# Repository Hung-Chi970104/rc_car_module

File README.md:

# Rukus: Pocket Robotics Control Computer
Welcome to Rukus! The most powerful and versatile pocket-size robotic control computer that can handle up 18V and 3.2A of peak current. It also features a powerful dual-core RP2040 MCU, allowing users to run heavy computing and even TinyML!

## Demo Video
https://github.com/user-attachments/assets/a237940f-da78-4733-91b2-979578ba8ca9

https://github.com/user-attachments/assets/f6da3c5c-2f20-4054-9eab-c4b8ad8e2e0a

## Components
- RP2040
- 12MHz Crystal (ABM8-272-T3)
- 4MB Flash Storage (W25Q16JVUXIQ)
- Buck-Boost Switching Regulator 5V to 3V3 (RT6150BGQW)
- Buck-Boost Switching Regulator 12V to 5V (AP64201)
- USB-C (TYPE-C-31-M-12)
- Motor Driver (TB6612FNG)

## PCBs
- 2 layers
- Single-sided component placement
- 2.6mm board thickness
- HASL (with lead) surface finish
- 1oz outer copper weight

### PCB Schematic

### PCB Layouts

### 3D Model

# How to order
- Download the zip file
- Upload the zip file to JLCPCB
- Select PCBA and continue
- Upload BOM.csv and position.csv
- Select the parts and submit payment

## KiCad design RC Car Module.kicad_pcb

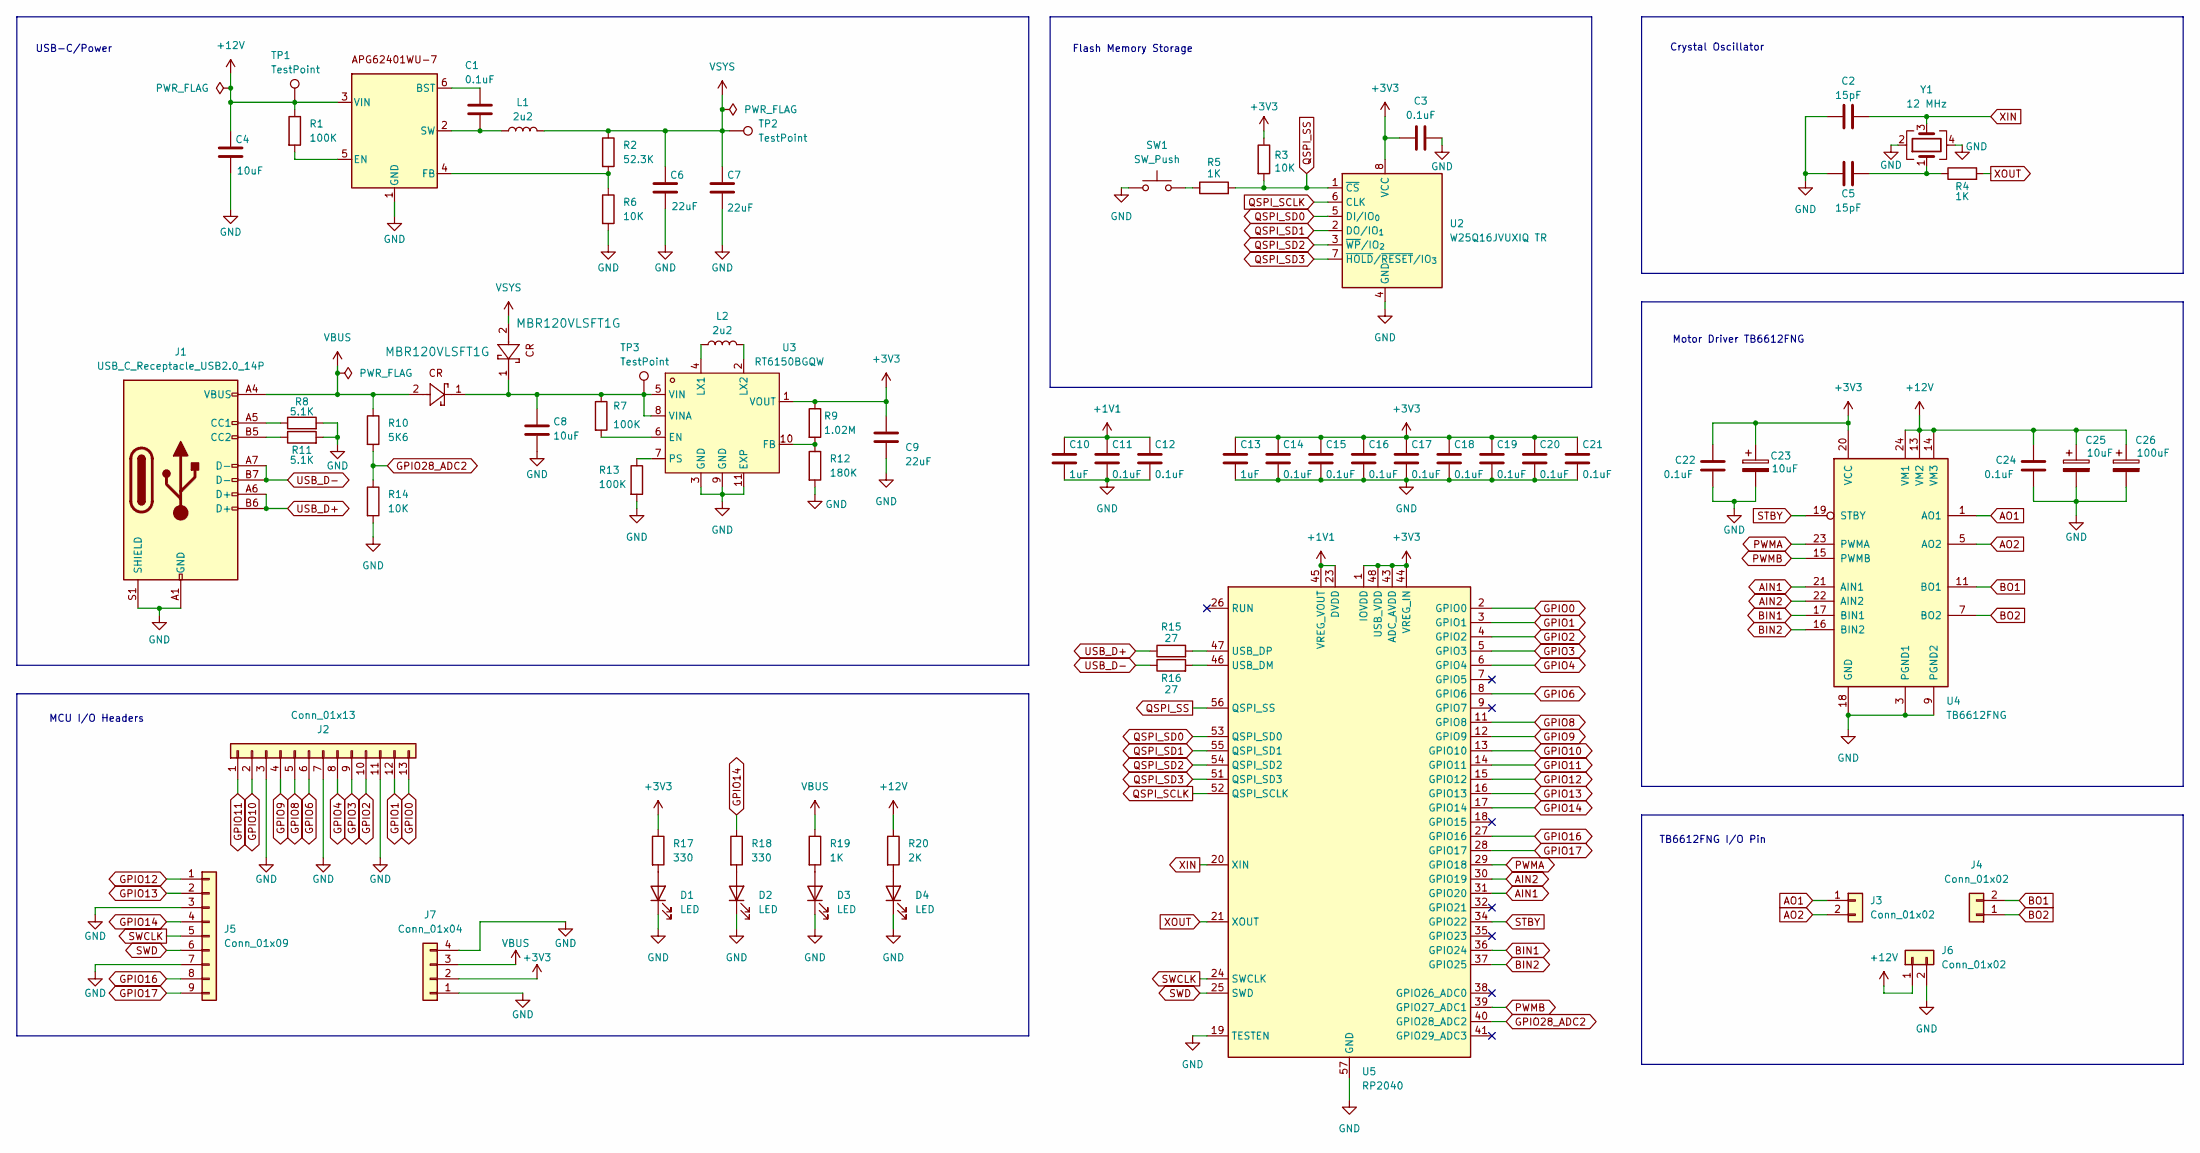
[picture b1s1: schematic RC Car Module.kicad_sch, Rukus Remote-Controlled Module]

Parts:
1111111111111, 11111111111111: MBR120VLSFT1G; SDO_SOD-123FL_ONS
C1, C3, C11, C12, C14, C15, C16, C17, C18, C19, C20, C21, C22, C24: 0.1uF; C_0402_1005Metric
C2, C5: 15pF; C_0402_1005Metric
C4, C8: 10uF; C_1206_3216Metric
C6, C7, C9: 22uF; C_1206_3216Metric
C10, C13: 1uF; C_0402_1005Metric
C23, C25: 10uF; CP_EIA-3528-15_AVX-H
C26: 100uF; CP_Elec_6.3x7.7
D1, D2, D3, D4: LED; LED_0805_2012Metric
J1: USB_C_Receptacle_USB2.0_14P; USB_C_Receptacle_HRO_TYPE-C-31-M-12
J2: Conn_01x13; PinHeader_1x13_P2.54mm_Vertical
J3, J4, J6: Conn_01x02; TerminalBlock_Phoenix_MKDS-1,5-2-5.08_1x02_P5.08mm_Horizont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
J5: Conn_01x09; PinHeader_1x09_P2.54mm_Vertical
J7: Conn_01x04; PinHeader_1x04_P2.54mm_Vertical
L1: 2u2; IND-SMD_L4.0-W4.0_XAL4030-332MEC
L2: 2u2; L_1008_2520Metric
R1, R7, R13: 100K; R_0402_1005Metric
R2: 52.3K; R_0402_1005Metric
R3, R6, R14: 10K; R_0402_1005Metric
R4, R5, R19: 1K; R_0402_1005Metric
R8, R11: 5.1K; R_0402_1005Metric
R9: 1.02M; R_0402_1005Metric
R10: 5K6; R_0402_1005Metric
R12: 180K; R_0402_1005Metric
R15, R16: 27; R_0402_1005Metric
R17, R18: 330; R_0402_1005Metric
R20: 2K; R_0402_1005Metric
SW1: SW_Push; SW_Push_SPST_NO_Alps_SKRK
TP1, TP2, TP3: TestPoint; TestPoint_Pad_1.0x1.0mm
U1: AP62401WU-7; SOT-23-6
U2: W25Q16JVUXIQ TR; Winbond_USON-8-1EP_3x2mm_P0.5mm_EP0.2x1.6mm
U3: RT6150BGQW; WSON-10_L2.5-W2.5-P0.50-BL-EP; LCSC Part C147972
U4: TB6612FNG; SSOP-24_5.3x8.2mm_P0.65mm
U5: RP2040; QFN-56-1EP_7x7mm_P0.4mm_EP3.2x3.2mm
Y1: 12 MHz; Crystal_SMD_3225-4Pin_3.2x2.5mm

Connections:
+1V1: C10.1, C11.1, C12.1, U5.23 (DVDD), U5.45 (VREG_VOUT), U5.50 (DVDD)
+3V3: C3.1, C9.1, C13.1, C14.1, C15.1, C16.1, C17.1, C18.1, C19.1, C20.1, C21.1, C22.1, C23.1, J7.2, R3.1, R9.1, R17.1, U2.8 (VCC), U3.1 (VOUT), U4.20 (VCC), U5.1 (IOVDD), U5.10 (IOVDD), U5.22 (IOVDD), U5.33 (IOVDD), U5.42 (IOVDD), U5.43 (ADC_AVDD), U5.44 (VREG_IN), U5.48 (USB_VDD), U5.49 (IOVDD)
+12V: C4.1, C24.1, C25.1, C26.1, J6.1, R1.1, R20.1, TP1.1, U1.3 (VIN), U4.13 (VM2), U4.14 (VM3), U4.24 (VM1)
AIN1: U4.21 (AIN1), U5.31 (GPIO20)
AIN2: U4.22 (AIN2), U5.30 (GPIO19)
AO1: J3.1, U4.1 (AO1), U4.2 (AO1)
AO2: J3.2, U4.5 (AO2), U4.6 (AO2)
BIN1: U4.17 (BIN1), U5.36 (GPIO24)
BIN2: U4.16 (BIN2), U5.37 (GPIO25)
BO1: J4.2, U4.11 (BO1), U4.12 (BO1)
BO2: J4.1, U4.7 (BO2), U4.8 (BO2)
GND: C2.1, C3.2, C4.2, C5.1, C6.2, C7.2, C8.2, C9.2, C10.2, C11.2, C12.2, C13.2, C14.2, C15.2, C16.2, C17.2, C18.2, C19.2, C20.2, C21.2, C22.2, C23.2, C24.2, C25.2, C26.2, D1.1 (K), D2.1 (K), D3.1 (K), D4.1 (K), J1.A1 (GND), J1.A12 (GND), J1.B1 (GND), J1.B12 (GND), J1.S1 (SHIELD), J2.3, J2.7, J2.11, J5.3, J5.7, J6.2, J7.1, J7.4, R6.2, R8.2, R11.2, R12.2, R13.2, R14.2, SW1.1, U1.1 (GND), U2.4 (GND), U3.3 (GND), U3.9 (GND), U3.11 (EXP), U4.3 (PGND1), U4.4 (PGND1), U4.9 (PGND2), U4.10 (PGND2), U4.18 (GND), U5.19 (TESTEN), U5.57 (GND), Y1.2, Y1.4
GPIO0: J2.13, U5.2 (GPIO0)
GPIO1: J2.12, U5.3 (GPIO1)
GPIO2: J2.10, U5.4 (GPIO2)
GPIO3: J2.9, U5.5 (GPIO3)
GPIO4: J2.8, U5.6 (GPIO4)
GPIO6: J2.6, U5.8 (GPIO6)
GPIO8: J2.5, U5.11 (GPIO8)
GPIO9: J2.4, U5.12 (GPIO9)
GPIO10: J2.2, U5.13 (GPIO10)
GPIO11: J2.1, U5.14 (GPIO11)
GPIO12: J5.1, U5.15 (GPIO12)
GPIO13: J5.2, U5.16 (GPIO13)
GPIO14: J5.4, R18.1, U5.17 (GPIO14)
GPIO16: J5.8, U5.27 (GPIO16)
GPIO17: J5.9, U5.28 (GPIO17)
GPIO28_ADC2: R10.2, R14.1, U5.40 (GPIO28_ADC2)
unnamed: C5.2, R4.1, Y1.1
unnamed: D1.2 (A), R17.2
unnamed: D2.2 (A), R18.2
unnamed: D3.2 (A), R19.2
unnamed: D4.2 (A), R20.2
unnamed: J1.A5 (CC1), R8.1
unnamed: J1.B5 (CC2), R11.1
unnamed: R5.1, SW1.2
unnamed: C1.1, U1.6 (BST)
unnamed: R1.2, U1.5 (EN)
unnamed: R2.2, R6.1, U1.4 (FB)
unnamed: C1.2, L1.1, U1.2 (SW)
unnamed: R7.2, U3.6 (EN)
unnamed: R9.2, R12.1, U3.10 (FB)
unnamed: L2.1, U3.4 (LX1)
unnamed: L2.2, U3.2 (LX2)
unnamed: R13.1, U3.7 (PS)
unnamed: 1111111111111.1, 11111111111111.1, C8.1, R7.1, TP3.1, U3.5 (VIN), U3.8 (VINA)
unnamed: R16.2, U5.46 (USB_DM)
unnamed: R15.2, U5.47 (USB_DP)
PWMA: U4.23 (PWMA), U5.29 (GPIO18)
PWMB: U4.15 (PWMB), U5.39 (GPIO27_ADC1)
QSPI_SCLK: U2.6 (CLK), U5.52 (QSPI_SCLK)
QSPI_SD0: U2.5 (DI/IO_{0}), U5.53 (QSPI_SD0)
QSPI_SD1: U2.2 (DO/IO_{1}), U5.55 (QSPI_SD1)
QSPI_SD2: U2.3 (~WP/IO_{2}), U5.54 (QSPI_SD2)
QSPI_SD3: U2.7 (~HOLD/~RESET/IO_{3}), U5.51 (QSPI_SD3)
QSPI_SS: R3.2, R5.2, U2.1 (~CS), U5.56 (QSPI_SS)
STBY: U4.19 (STBY), U5.34 (GPIO22)
SWCLK: J5.5, U5.24 (SWCLK)
SWD: J5.6, U5.25 (SWD)
USB_D+: J1.A6 (D+), J1.B6 (D+), R15.1
USB_D-: J1.A7 (D-), J1.B7 (D-), R16.1
VBUS: 1111111111111.2, J1.A4 (VBUS), J1.A9 (VBUS), J1.B4 (VBUS), J1.B9 (VBUS), J7.3, R10.1, R19.1
VSYS: 11111111111111.2, C6.1, C7.1, L1.2, R2.1, TP2.1
XIN: C2.2, U5.20 (XIN), Y1.3
XOUT: R4.2, U5.21 (XOUT)

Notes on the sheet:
USB-C/Power
Flash Memory Storage
Motor Driver TB6612FNG
Crystal Oscillator
TB6612FNG I/O Pin
MCU I/O Headers

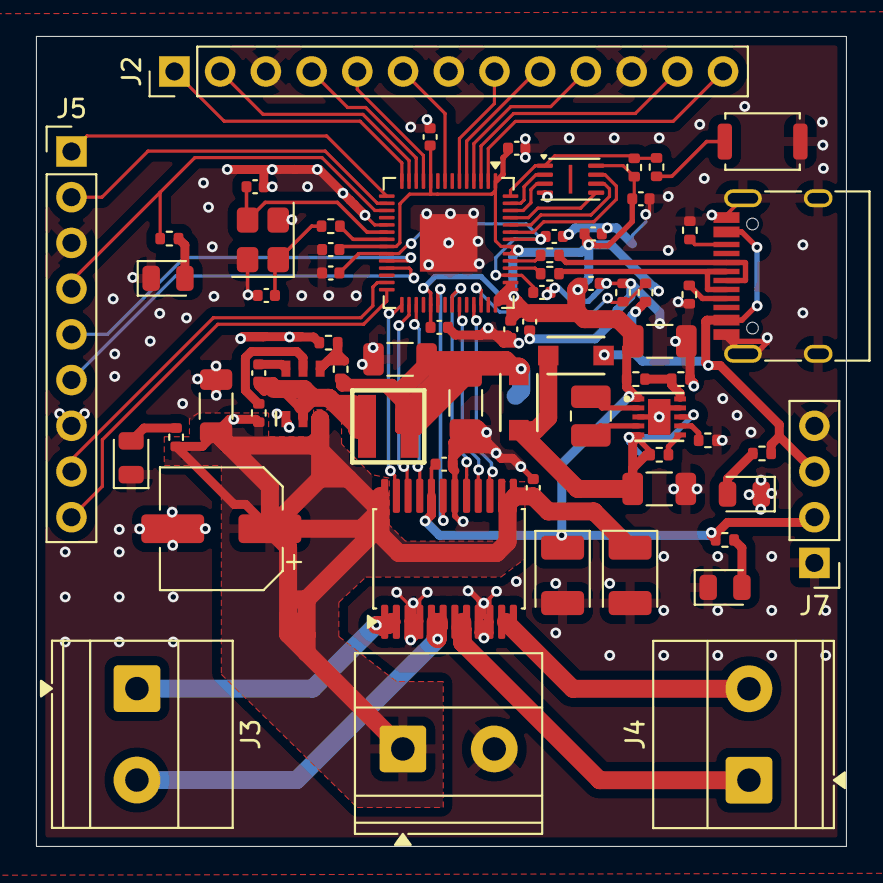
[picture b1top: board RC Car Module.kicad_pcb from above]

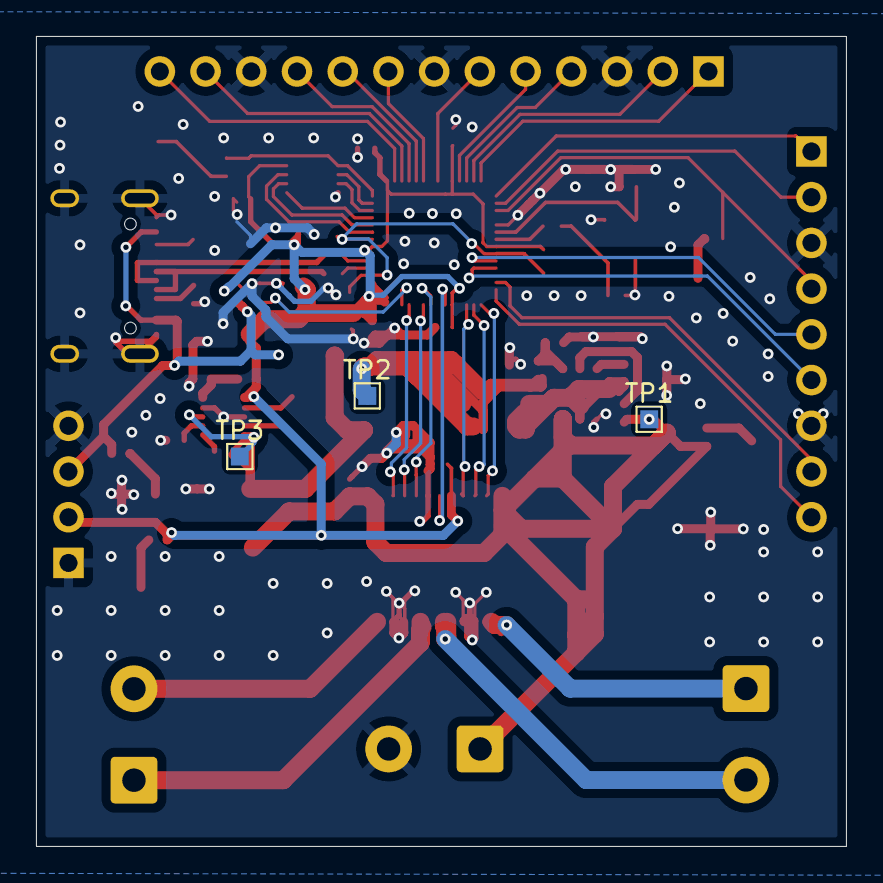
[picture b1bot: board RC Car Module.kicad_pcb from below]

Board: 2 copper layers, 45.0 x 45.0 mm, 70 parts (3 on the bottom side), 65 nets.

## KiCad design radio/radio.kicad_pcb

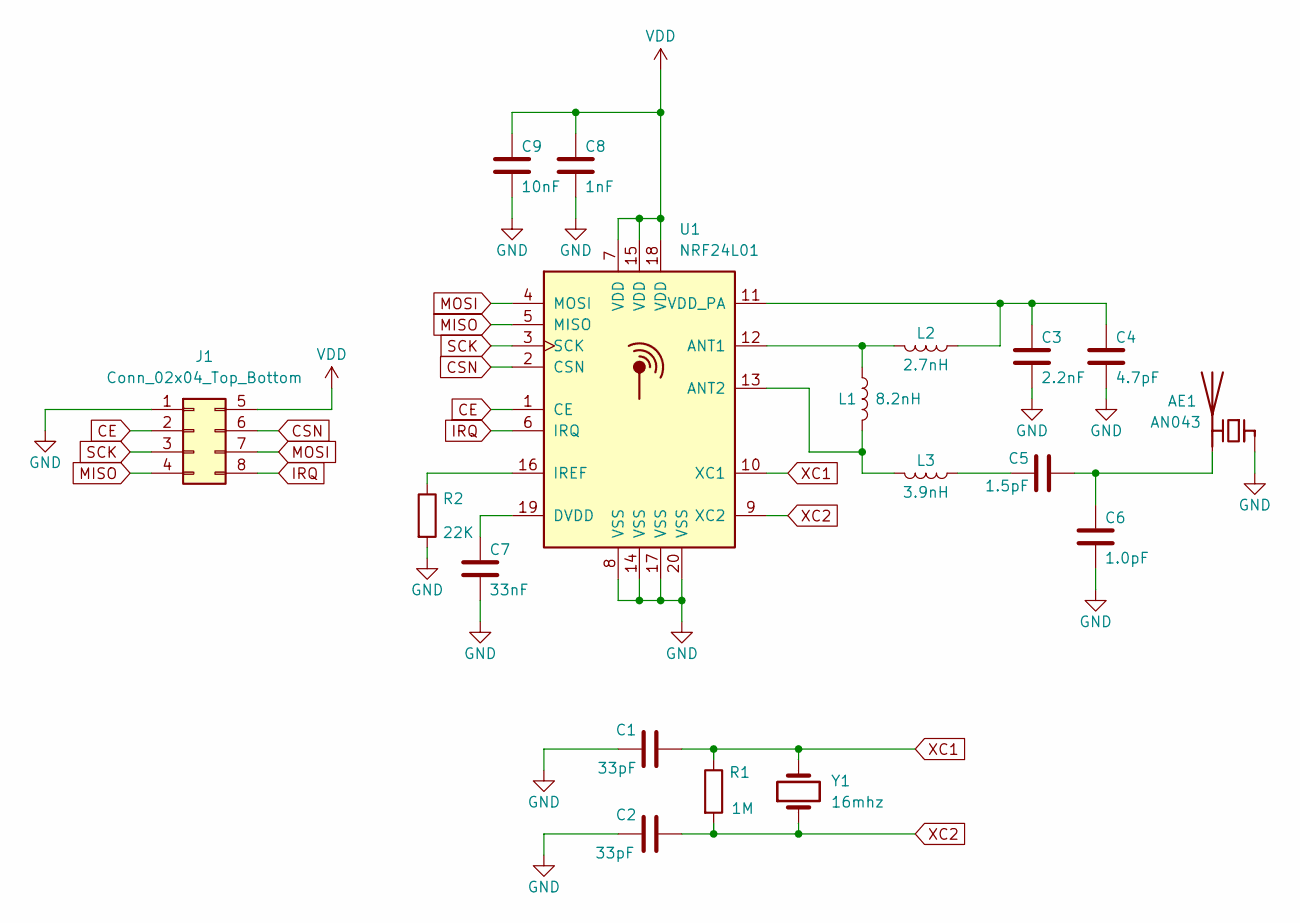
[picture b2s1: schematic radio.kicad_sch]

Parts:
AE1: AN043
C1, C2: 33pF; C_0402_1005Metric
C3: 2.2nF; C_0402_1005Metric
C4: 4.7pF; C_0402_1005Metric
C5: 1.5pF; C_0402_1005Metric
C6: 1.0pF; C_0402_1005Metric
C7: 33nF; C_0402_1005Metric
C8: 1nF; C_0402_1005Metric
C9: 10nF; C_0402_1005Metric
J1: Conn_02x04_Top_Bottom; PinHeader_2x04_P2.54mm_Vertical
L1: 8.2nH; L_0402_1005Metric
L2: 2.7nH; L_0402_1005Metric
L3: 3.9nH; L_0402_1005Metric
R1: 1M; R_0402_1005Metric
R2: 22K; R_0402_1005Metric
U1: NRF24L01; QFN-20-1EP_4x4mm_P0.5mm_EP2.5x2.5mm
Y1: 16mhz; Crystal_HC49-4H_Vertical

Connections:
CE: J1.2, U1.1 (CE)
CSN: J1.6, U1.2 (CSN)
GND: AE1.1 (FEED), C1.1, C2.1, C3.2, C4.2, C6.2, C7.2, C8.2, C9.2, J1.1, R2.2, U1.8 (VSS), U1.14 (VSS), U1.17 (VSS), U1.20 (VSS)
IRQ: J1.8, U1.6 (IRQ)
MISO: J1.4, U1.5 (MISO)
MOSI: J1.7, U1.4 (MOSI)
unnamed: AE1.2 (PCB_Trace), C5.2, C6.1
unnamed: C5.1, L3.1
unnamed: L1.1, L2.2, U1.12 (ANT1)
unnamed: L1.2, L3.2, U1.13 (ANT2)
unnamed: C7.1, U1.19 (DVDD)
unnamed: R2.1, U1.16 (IREF)
unnamed: C3.1, C4.1, L2.1, U1.11 (VDD_PA)
SCK: J1.3, U1.3 (SCK)
VDD: C8.1, C9.1, J1.5, U1.7 (VDD), U1.15 (VDD), U1.18 (VDD)
XC1: C1.2, R1.1, U1.10 (XC1), Y1.2
XC2: C2.2, R1.2, U1.9 (XC2), Y1.1

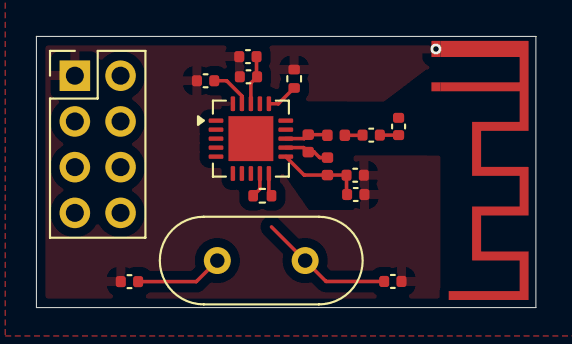
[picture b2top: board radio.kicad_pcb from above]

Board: 2 copper layers, 27.7 x 15.1 mm, 18 parts (0 on the bottom side), 17 nets.

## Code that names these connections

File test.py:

import sys
import uselect
from machine import Pin, PWM
import time

# --- 1. Motor Setup ---
stby = Pin(22, Pin.OUT)
stby.value(1) # Enable driver

pwma = PWM(Pin(18))
pwma.freq(1000)
ain1 = Pin(20, Pin.OUT)
ain2 = Pin(19, Pin.OUT)

pwmb = PWM(Pin(27))
pwmb.freq(1000)
bin1 = Pin(24, Pin.OUT)
bin2 = Pin(25, Pin.OUT)

# Default speed (0 to 65535). 40000 is about 60% speed.
SPEED = 40000 

# --- 2. Movement Functions ---
def move_forward():
    ain1.value(1); ain2.value(0); pwma.duty_u16(SPEED)
    bin1.value(1); bin2.value(0); pwmb.duty_u16(SPEED)
    print("Moving: FORWARD")

def move_backward():
    ain1.value(0); ain2.value(1); pwma.duty_u16(SPEED)
    bin1.value(0); bin2.value(1); pwmb.duty_u16(SPEED)
    print("Moving: BACKWARD")

def turn_left():
    # Motor A backwards, Motor B forwards (Tank turn)
    ain1.value(0); ain2.value(1); pwma.duty_u16(SPEED)
    bin1.value(1); bin2.value(0); pwmb.duty_u16(SPEED)
    print("Turning: LEFT")

def turn_right():
    # Motor A forwards, Motor B backwards
    ain1.value(1); ain2.value(0); pwma.duty_u16(SPEED)
    bin1.value(0); bin2.value(1); pwmb.duty_u16(SPEED)
    print("Turning: RIGHT")

def stop_motors():
    ain1.value(0); ain2.value(0); pwma.duty_u16(0)
    bin1.value(0); bin2.value(0); pwmb.duty_u16(0)
    print("Motors: STOPPED")

# --- 3. Keyboard Input Setup ---
# We use 'uselect' to read keystrokes instantly without needing to press "Enter"
poll_obj = uselect.poll()
poll_obj.register(sys.stdin, uselect.POLLIN)

print("\n" + "="*30)
print("🚀 LIVE DEMO MODE ACTIVE 🚀")
print("="*30)
print("IMPORTANT: Click your mouse inside this Shell/Console window first!")
print("Controls:")
print("  [W] = Forward")
print("  [S] = Backward")
print("  [A] = Turn Left")
print("  [D] = Turn Right")
print("  [Space] = Stop")
print("  [Q] = Quit Demo")
print("Waiting for input...\n")

try:
    while True:
        # Check if a key was pressed
        poll_results = poll_obj.poll(10) # check every 10ms
        
        if poll_results:
            # Read exactly one character
            char = sys.stdin.read(1).lower()
            
            if char == 'w':
                print("going forward")
                move_forward()
            elif char == 's':
                move_backward()
            elif char == 'a':
                turn_left()
            elif char == 'd':
                turn_right()
            elif char == ' ':
                stop_motors()
            elif char == 'q':
                print("\nExiting demo...")
                break # Break the loop and finish

except KeyboardInterrupt:
    print("\nDemo interrupted.")

finally:
    # Always shut down safely when exiting
    stop_motors()
    stby.value(0)
    print("Power off. Safe to disconnect.")

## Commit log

2026-02-07 Add readme
2026-02-07 Add production folders
2026-02-15 Began adding radio and made a couple changes to the footprints
2026-04-30 Add demo video links to README
    Added demo video links to README.
2026-04-30 Update README with additional demo video link
    Added a demo video link to the README.
2026-04-30 Update assets
